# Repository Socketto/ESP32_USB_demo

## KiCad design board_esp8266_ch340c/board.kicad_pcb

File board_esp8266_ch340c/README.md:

# ESP8266 + CH340B USB board

Independent KiCad 10 project using an **ESP-12F** and a **CH340B** USB-to-UART
bridge. The ESP8266 + CP2102N project and its routed PCB are unchanged.

> **Prototype pending review.** The board is routed, but two USB connector
> hole-clearance errors and two via-in-pad locations remain. Obtain JLCPCB's
> acceptance of the USB geometry and review assembly risks before ordering.
> Electrical and thermal performance still require physical testing.

## Opening the project

Open `board.kicad_pro` in this directory. Keep `esp8266_usb.kicad_sym` and
`sym-lib-table` alongside it: they supply the local
`ESP8266_USB:CH340B_3V3` symbol.

The local symbol reflects the CH340B's pin functions. V3 pin 4 is a power
**input** in this externally supplied 3.3 V configuration, rather than the
regulator output used in 5 V operation.

## USB bridge and power

| Designator | Component | JLCPCB / LCSC |
| --- | --- | --- |
| U1 | Ai-Thinker ESP-12F | C82891 |
| U4 | WCH CH340B, SOP-16 | C81010 |
| U3 | TI TLV1117LV33DCYR, ceramic-stable 3.3 V regulator | C15578 |
| USB1 | HC-TYPE-C-16P-01A USB-C connector | C2894897 |
| D1 | ROHM SMLVN6RGB1U1 RGB LED, unchanged | C2909770 |

**C81010 is Extended**, not Basic. Check current stock, price and feeder
charges in the actual JLCPCB quotation. This variant does not substitute an
unverified Basic RGB 5050.

USB1 supplies +5V to U3. CH340B **VCC pin 16 and V3 pin 4 both connect to
+3V3**; neither connects to +5V. No crystal is required. Unlike CH340C,
CH340B pin 15 is the TNOW output and must not be connected to GND.

| CH340B pin | Connection |
| --- | --- |
| 1, GND | GND |
| 2, TXD | ESP8266 GPIO3 / U0RXD |
| 3, RXD | ESP8266 GPIO1 / U0TXD |
| 4, V3; 16, VCC | +3V3 |
| 5, UD+ | USB1 A6/B6 |
| 6, UD- | USB1 A7/B7 |
| 7, RST# | Unconnected; internal pull-up |
| 8-12 | Unused; intentionally left unconnected |
| 13, DTR# | PROG_DTR, transistor auto-reset circuit |
| 14, RTS# | PROG_RTS, transistor auto-reset circuit |
| 15, TNOW | Unconnected output |

The CP2102N-specific VBUS divider R14/R15 and reset pull-up R22 have been
removed, together with their schematic wiring and obsolete nets. CH340B
has internal power-on reset and needs neither circuit.

## Automatic programming

The existing two-MMBT3904 circuit is retained:

- DTR drives Q1's base through R18 (10 kOhm) and Q2's emitter.
- RTS drives Q2's base through R19 (10 kOhm) and Q1's emitter.
- Q1's collector controls ESP_EN; Q2's collector controls GPIO0.

| DTR pin level | RTS pin level | ESP_EN | GPIO0 |
| --- | --- | --- | --- |
| High | High | High | High |
| Low | Low | High | High |
| High | Low | Low | High |
| Low | High | High | Low |

These are **physical signal levels**, not serial API boolean values:
DTR#/RTS# are active low. The topology supports the ESP8266 `esptool`
automatic reset/download sequence without manual BOOT/RESET jumpers.
Disable terminal hardware flow control. Install the WCH CH340 driver if
the operating system does not provide it.

R5 (10 kOhm) and C6 (1 uF) set EN reset timing. R6 pulls GPIO0 high,
R13 pulls GPIO2 high, and R12 pulls GPIO15 low (all 10 kOhm).
Normal flash boot requires GPIO0/GPIO2 high and GPIO15 low; downloading
requires GPIO0 low at reset. ESP8266 EN and RST remain tied together as in
the source variant. Verify power-up, automatic uploads and the return to
normal boot on a physical prototype.

## Placement and routing

U4 now uses `Package_SO:SOIC-16_3.9x9.9mm_P1.27mm`, not the CP2102N QFN.
It is placed 1 mm below the former bridge position. C9 (100 nF) and C7
(4.7 uF) have been repositioned around it; C1 remains a 100 nF bypass.
Keep USB D+/D- together, short and away from the antenna. The revised D-
route follows D+ more closely, but the pair has not been impedance-controlled
or simulated.

C8 (100 nF) and C11 (4.7 uF) remain at ESP VCC. C6 remains near EN/RST.
Preserve the ESP-12F footprint's antenna keepout on both copper layers.
The +3V3 supply has a wider parallel B.Cu track and a local F.Cu copper
area at U3's tab. The long supply and remaining narrow segments still require
voltage-drop and temperature measurements under Wi-Fi load. Retain the
ceramic-stable TLV1117LV regulator and C5 (22 uF), rather than making an
unchecked AMS1117 substitution.

The board outline includes physical letter-shaped cutouts on Edge.Cuts;
check that these are intentional in JLCPCB's Gerber viewer. The ESP antenna
keepout and USB connector footprint, including its holes, are unchanged.

## Firmware connections

| Function | ESP8266 pin | Circuit |
| --- | --- | --- |
| RGB red | GPIO12 / D6 | R2, 330 Ohm, to red anode |
| RGB green | GPIO13 / D7 | R3, 330 Ohm, to green anode |
| RGB blue | GPIO14 / D5 | R1, 330 Ohm, to blue anode |
| Digital input | GPIO4 / D2 | IN1, active high; R8 external 10 kOhm pull-down |
| Analog input | TOUT / ADC0 / A0 | TH1 NTC and R23/R24/R25 divider |
| Recovery input | GPIO5 / D1 | DA1, normally open; close to GND during boot |

D1 retains its existing ROHM footprint and common-ground cathodes.
R1/R2/R3 remain 330 Ohm. Green and blue may be dim at 3.3 V; verify their
brightness on the prototype before changing resistors. A future 5050
substitution requires a verified part number, pinout, polarity and resistor
review.

TH1 is a 10 kOhm B3950 NTC. R23 (10 kOhm) supplies the thermistor divider;
R24 (33 kOhm) and R25 (10 kOhm) attenuate its output for the ESP8266's
0-1.0 V ADC. Including divider loading, nominal ADC voltage is about
0.344 V at 25 C and 0.623 V with an open thermistor. Firmware reads A0
as a raw 10-bit value, 0..1023, exposed as `REAL`; do not apply 3.3 V
directly to TOUT.

DA1 connects GPIO5 to GND for recovery, not to the ADC or ROM boot strap.
Firmware must enable GPIO5's pull-up and sample DA1 during boot to restore
the default application and parameters. DA1 remains excluded from the
assembly BOM and CPL.

## JLCPCB manufacturing files

Use **[bouni/kicad-jlcpcb-tools](https://github.com/bouni/kicad-jlcpcb-tools)**,
listed as *JLCPCB Tools* in KiCad's Plugin and Content Manager.
This variant has its own `jlcpcb/project.db` with U4 assigned to C81010
and R14/R15/R22 removed.

The database retains the transistor and ROHM LED orientation corrections.
It includes a `^CH340B$` rule of +270 degrees,
following the plugin's SOP/SOIC convention. With the current PCB angles,
U4 exports at 270 degrees, Q1/Q2 at 180 degrees and D1 at 180 degrees.
These are **CPL corrections**, not instructions to rotate the PCB footprints.
Confirm every component's pin 1 against JLCPCB's assembly preview.

The current exports are in `jlcpcb/production_files`: Gerber and drill ZIP,
BOM and CPL were generated from this PCB and its local plugin database.
Regenerate all of them together after any design change; do not mix them
with exports from the CP2102N or ESP32 projects. Inspect the Gerbers and
the placement preview, including pin 1 and polarity, before ordering.

## Images

Images are design previews, not fabrication approval.

## Current checks and remaining work

Schematic ERC: no errors; one inherited D4 LED-library mismatch warning.
PCB DRC: no unconnected items or schematic-parity issues; two USB1
hole-clearance errors remain. The clearance is 0.1847 mm versus the
project's 0.25 mm requirement. The connector holes have deliberately not
been changed: **JLCPCB must confirm that they can manufacture this geometry**.

Seventeen vias were moved outside SMD pads. Two remain in pads: U4 pin 5
(USB D+) and D4 pin 1 (GND). Although the vias are tented, the pad's mask
opening can expose the hole and cause solder wicking. Ask JLCPCB about
their assembly process or move/fill these vias before ordering.

Prototype checks must cover USB enumeration, both UART directions,
automatic programming/reset, ESP Wi-Fi power stability and regulator
temperature, RGB brightness, digital input, NTC ADC and firmware recovery.

References:
[WCH CH340 datasheet](https://www.wch-ic.com/downloads/CH340DS1_PDF.html) and
[Espressif ESP8266 boot mode selection](https://docs.espressif.com/projects/esptool/en/latest/esp8266/advanced-topics/boot-mode-selection.html);
[JLCPCB via-in-pad guidance](https://jlcpcb.com/blog/via-in-pad-pcb).

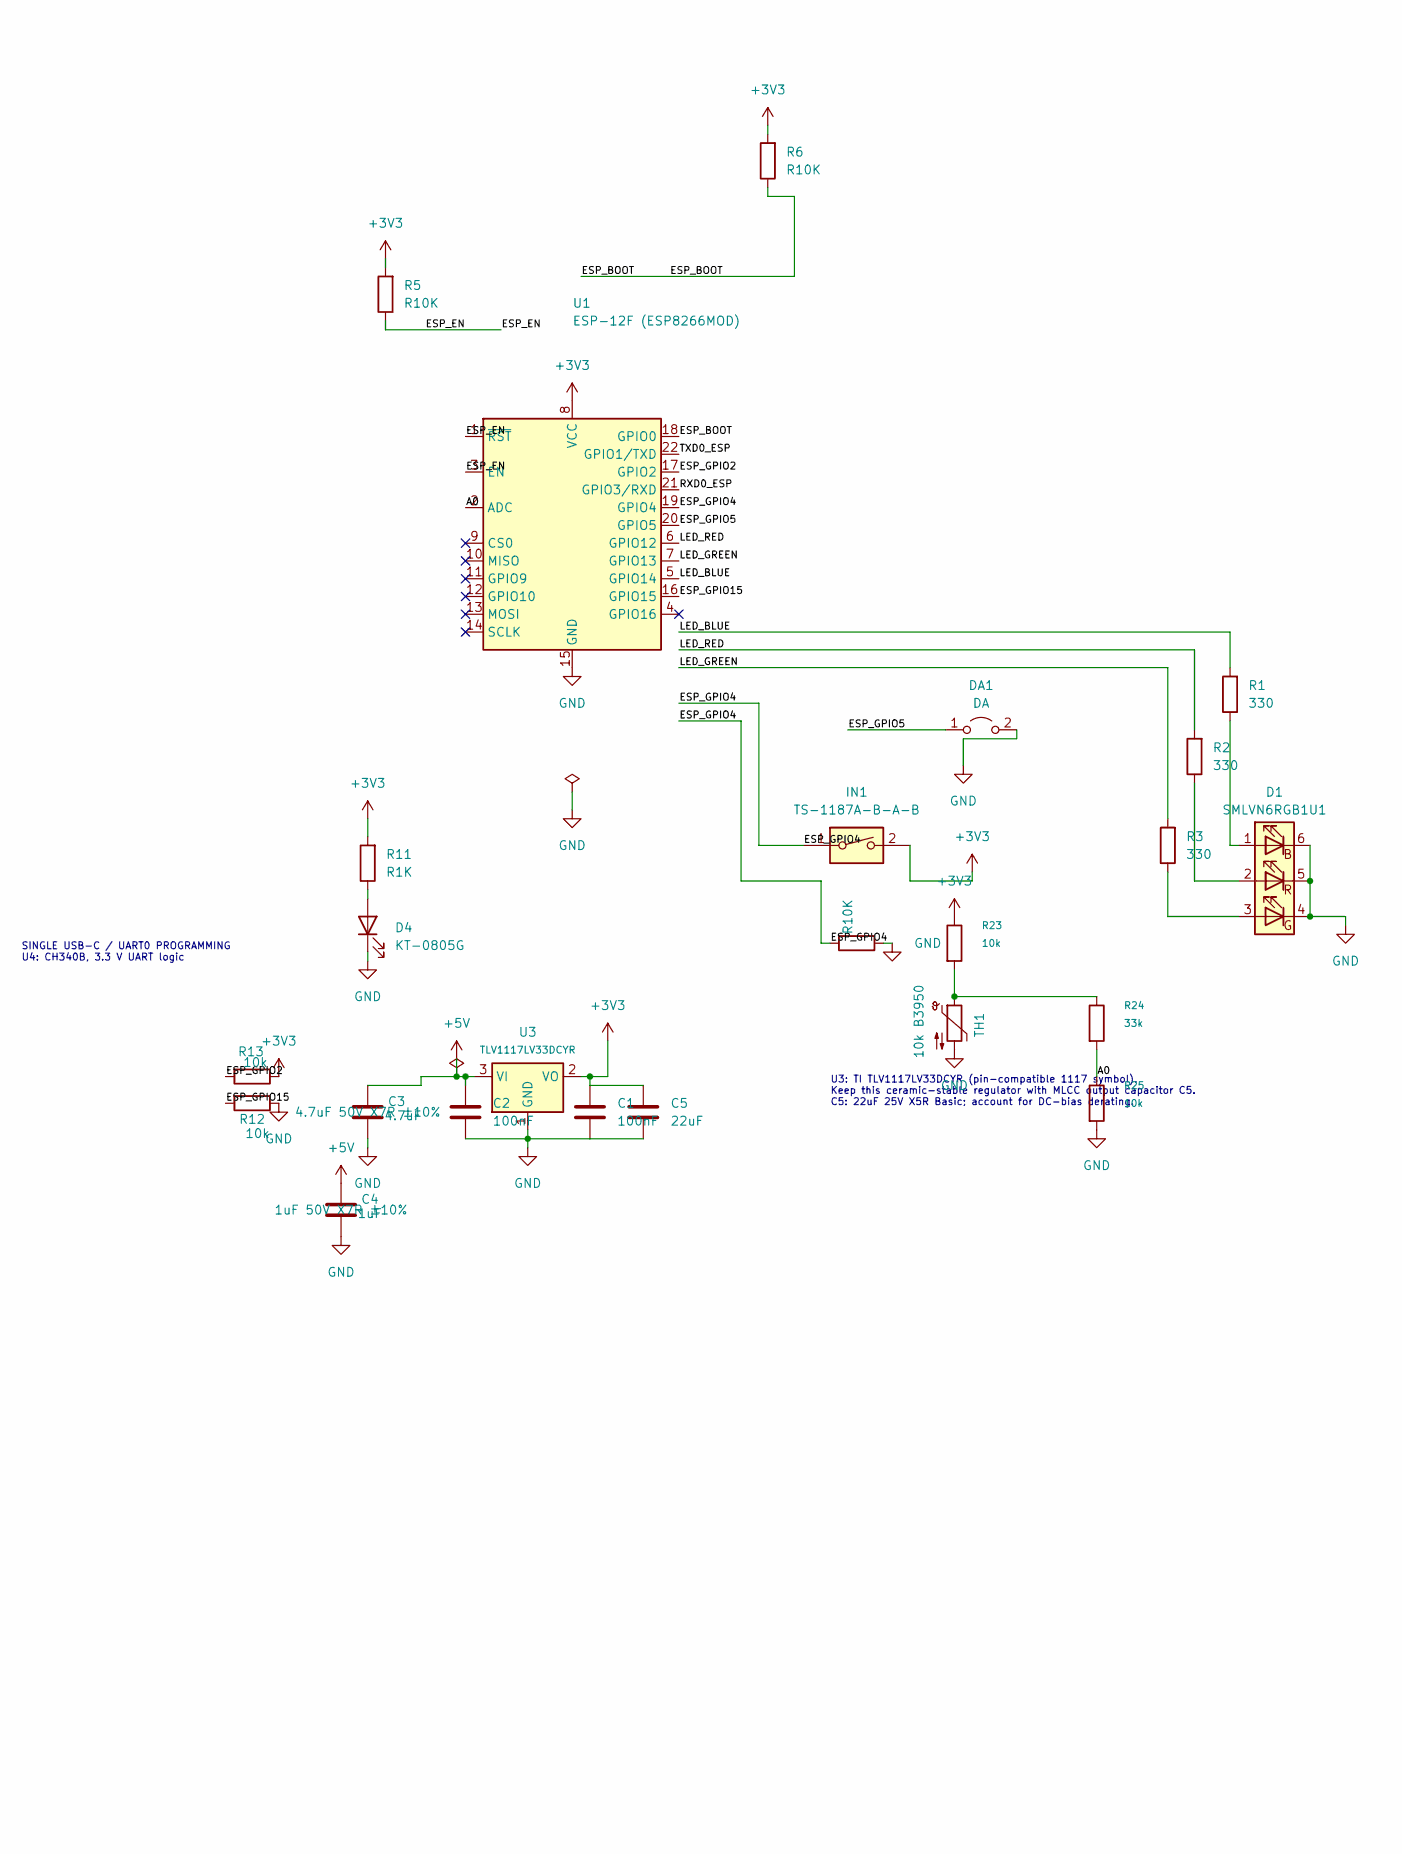
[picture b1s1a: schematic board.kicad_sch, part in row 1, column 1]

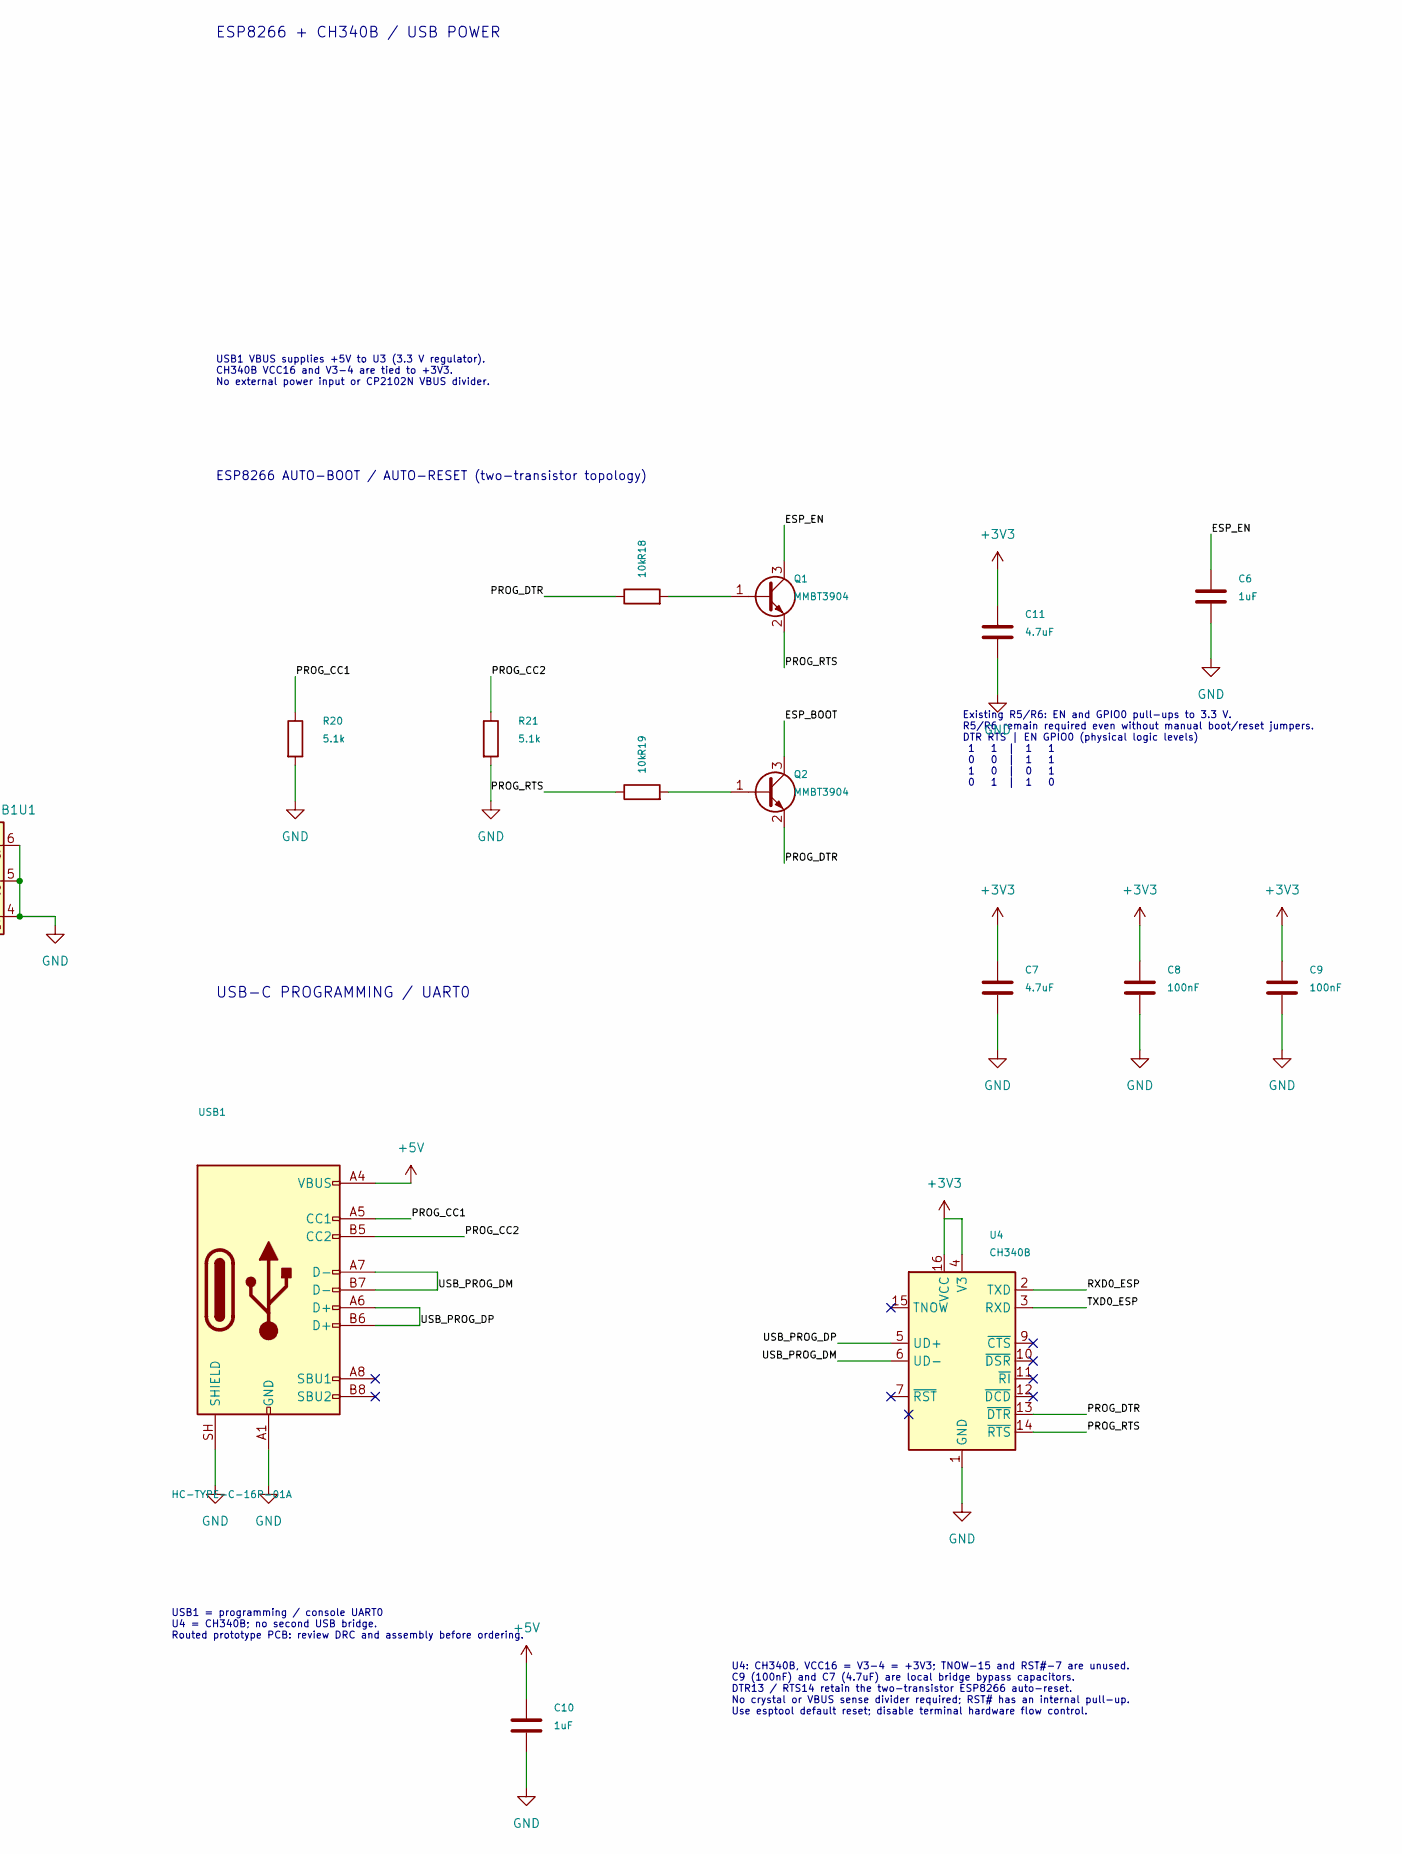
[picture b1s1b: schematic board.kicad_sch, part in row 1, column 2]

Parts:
C1, C2, C8, C9: 100nF; C_1206_3216Metric; MPN CL31B104KBCNNNC; LCSC C24497
C3, C7, C11: 4.7uF; C_1206_3216Metric; MPN 1206B475K500NT; LCSC C29823
C4, C6, C10: 1uF; C_1206_3216Metric; MPN CL31B105KBHNNNE; LCSC C1848
C5: 22uF; C_1206_3216Metric; MPN CL31A226KAHNNNE; LCSC C12891
D1: SMLVN6RGB1U1; LED_ROHM_SMLVN6; MPN SMLVN6RGB1U1; LCSC C2909770
D4: KT-0805G; LED_0805_2012Metric; MPN KT-0805G; LCSC C2297
DA1: DA; PinHeader_2x01_P2.54mm_Vertical
IN1: TS-1187A-B-A-B; SW_Push_1P1T_XKB_TS-1187A; MPN TS-1187A-B-A-B; LCSC C318884
Q1, Q2: MMBT3904; SOT-23; MPN MMBT3904(RANGE:100-300); LCSC C20526
R1, R2, R3: 330; R_1206_3216Metric; MPN 1206W4F3300T5E; LCSC C17930
R5, R6, R8: R10K; R_1206_3216Metric; MPN 1206W4F1002T5E; LCSC C17902
R11: R1K; R_1206_3216Metric; MPN 1206W4F1001T5E; LCSC C4410
R12, R13, R25: 10k; R_0603_1608Metric; MPN 0603WAF1002T5E; LCSC C25804
R18, R19, R23: 10k; R_1206_3216Metric; MPN 1206W4F1002T5E; LCSC C17902
R20, R21: 5.1k; R_0603_1608Metric; MPN 0603WAF5101T5E; LCSC C23186
R24: 33k; R_0603_1608Metric; MPN 0603WAF3302T5E; LCSC C4216
TH1: 10k B3950; R_0805_2012Metric; MPN CMFB103J3950HANT; LCSC C338623
U1: ESP-12F (ESP8266MOD); ESP-12E; MPN ESP-12F(ESP8266MOD); LCSC C82891
U3: TLV1117LV33DCYR; SOT-223-3_TabPin2; MPN TLV1117LV33DCYR; LCSC C15578
U4: CH340B; SOIC-16_3.9x9.9mm_P1.27mm; MPN CH340B; LCSC C81010
USB1: HC-TYPE-C-16P-01A; USB_C_Receptacle_HCTL_HC-TYPE-C-16P-01A; MPN HC-TYPE-C-16P-01A; LCSC C2894897

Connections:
+3V3: C1.1, C5.1, C7.1, C8.1, C9.1, C11.1, IN1.2, R5.2, R6.2, R11.2, R13.1, R23.1, U1.8 (VCC), U3.2 (VO), U4.4 (V3), U4.16 (VCC)
+5V: C2.1, C3.1, C4.1, C10.1, U3.3 (VI), USB1.A4 (VBUS), USB1.A9 (VBUS), USB1.B4 (VBUS), USB1.B9 (VBUS)
/A0: R24.2, R25.1, U1.2 (ADC)
/ESP_BOOT: Q2.3 (C), R6.1, U1.18 (GPIO0)
/ESP_EN: C6.1, Q1.3 (C), R5.1, U1.1 (~RST), U1.3 (EN)
/ESP_GPIO2: R13.2, U1.17 (GPIO2)
/ESP_GPIO4: IN1.1, R8.2, U1.19 (GPIO4)
/ESP_GPIO5: DA1.1 (A), U1.20 (GPIO5)
/ESP_GPIO15: R12.2, U1.16 (GPIO15)
/LED_BLUE: R1.2, U1.5 (GPIO14)
/LED_GREEN: R3.2, U1.7 (GPIO13)
/LED_RED: R2.2, U1.6 (GPIO12)
/PROG_CC1: R20.1, USB1.A5 (CC1)
/PROG_CC2: R21.1, USB1.B5 (CC2)
/PROG_DTR: Q2.2 (E), R18.1, U4.13 (~DTR)
/PROG_RTS: Q1.2 (E), R19.1, U4.14 (~RTS)
/RXD0_ESP: U1.21 (GPIO3/RXD), U4.2 (TXD)
/TXD0_ESP: U1.22 (GPIO1/TXD), U4.3 (RXD)
/USB_PROG_DM: U4.6 (UD-), USB1.A7 (D-), USB1.B7 (D-)
/USB_PROG_DP: U4.5 (UD+), USB1.A6 (D+), USB1.B6 (D+)
GND: C1.2, C2.2, C3.2, C4.2, C5.2, C6.2, C7.2, C8.2, C9.2, C10.2, C11.2, D1.4 (GK), D1.5 (RK), D1.6 (BK), D4.1 (K), DA1.2 (B), R8.1, R12.1, R20.2, R21.2, R25.2, TH1.2, U1.15 (GND), U3.1 (GND), U4.1 (GND), USB1.A1 (GND), USB1.A12 (GND), USB1.B1 (GND), USB1.B12 (GND), USB1.SH (SHIELD)
unnamed: D1.1 (BA), R1.1
unnamed: D1.3 (GA), R3.1
unnamed: D1.2 (RA), R2.1
unnamed: D4.2 (A), R11.1
unnamed: Q1.1 (B), R18.2
unnamed: Q2.1 (B), R19.2
unnamed: R23.2, R24.1, TH1.1

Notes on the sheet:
SINGLE USB-C / UART0 PROGRAMMING U4: CH340B, 3.3 V UART logic
ESP8266 + CH340B / USB POWER
USB1 = programming / console UART0 U4 = CH340B; no second USB bridge. Routed prototype PCB: review DRC and assembly before ordering.
USB-C PROGRAMMING / UART0
USB1 VBUS supplies +5V to U3 (3.3 V regulator). CH340B VCC16 and V3-4 are tied to +3V3. No external power input or CP2102N VBUS divider.
U4: CH340B, VCC16 = V3-4 = +3V3; TNOW-15 and RST#-7 are unused. C9 (100nF) and C7 (4.7uF) are local bridge bypass capacitors. DTR13 / RTS14 retain the two-transistor ESP8266 auto-reset. No crystal or VBUS sense divider required; RST# has an internal pull-up. Use esptool default reset; disable termi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
U3: TI TLV1117LV33DCYR (pin-compatible 1117 symbol). Keep this ceramic-stable regulator with MLCC output capacitor C5. C5: 22uF 25V X5R Basic; account for DC-bias derating.
ESP8266 AUTO-BOOT / AUTO-RESET (two-transistor topology)
Existing R5/R6: EN and GPIO0 pull-ups to 3.3 V. R5/R6 remain required even without manual boot/reset jumpers. DTR RTS | EN GPIO0 (physical logic levels) 1 1 | 1 1 0 0 | 1 1 1 0 | 0 1 0 1 | 1 0

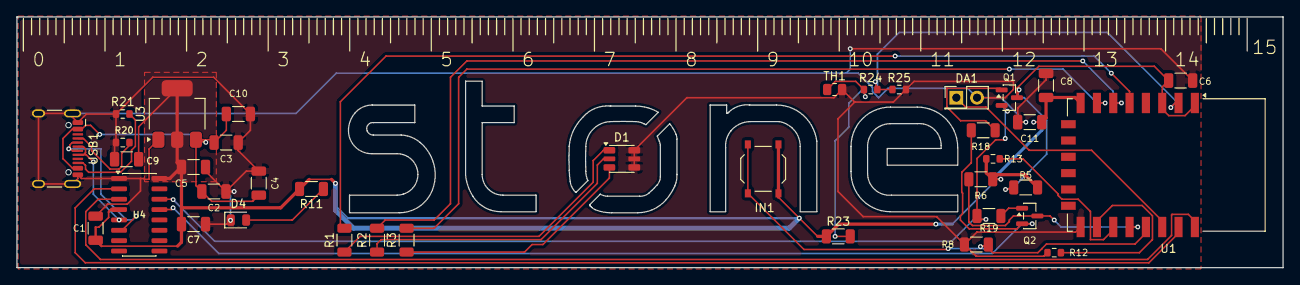
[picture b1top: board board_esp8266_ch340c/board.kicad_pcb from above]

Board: 2 copper layers, 155.2 x 30.7 mm, 38 parts (0 on the bottom side), 28 nets.

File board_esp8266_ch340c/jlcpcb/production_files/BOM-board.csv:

Comment,Designator,Footprint,LCSC,Quantity
100nF,"C1,C2,C8,C9",C_1206_3216Metric,C24497,4
10k,"R18,R19,R23",R_1206_3216Metric,C17902,3
10k,"R12,R13,R25",R_0603_1608Metric,C25804,3
10k B3950,TH1,R_0805_2012Metric,C338623,1
1uF,"C10,C4,C6",C_1206_3216Metric,C1848,3
22uF,C5,C_1206_3216Metric,C12891,1
330,"R1,R2,R3",R_1206_3216Metric,C17930,3
33k,R24,R_0603_1608Metric,C4216,1
4.7uF,"C11,C3,C7",C_1206_3216Metric,C29823,3
5.1k,"R20,R21",R_0603_1608Metric,C23186,2
CH340B,U4,SOIC-16_3.9x9.9mm_P1.27mm,C81010,1
ESP-12F (ESP8266MOD),U1,ESP-12E,C82891,1
HC-TYPE-C-16P-01A,USB1,USB_C_Receptacle_HCTL_HC-TYPE-C-16P-01A,C2894897,1
KT-0805G,D4,LED_0805_2012Metric,C2297,1
MMBT3904,"Q1,Q2",SOT-23,C20526,2
R10K,"R5,R6,R8",R_1206_3216Metric,C17902,3
R1K,R11,R_1206_3216Metric,C4410,1
SMLVN6RGB1U1,D1,LED_ROHM_SMLVN6,C2909770,1
TLV1117LV33DCYR,U3,SOT-223-3_TabPin2,C15578,1
TS-1187A-B-A-B,IN1,SW_Push_1P1T_XKB_TS-1187A,C318884,1

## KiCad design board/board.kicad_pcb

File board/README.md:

# ESP32 USB demo - KiCad board

ESP32-WROOM-32E-N4 demonstration board with one USB-C port, a WCH CH340C
application USB-to-UART bridge, external UART0 programming headers, a 3.3 V
regulator, and a TFT SPI connector.

> **Work in progress, not production-ready.** The PCB has no tracks, vias,
> or copper zones. Exported Gerber, BOM, and CPL files are placement snapshots,
> not a finished board suitable for ordering. Complete routing and resolve
> manufacturing issues before fabrication.
>
> **Connect either the external programmer or Serial1 USB, never both.**
> During programming, the programmer supplies regulated 3.3 V through J2.
> Disconnect the programmer completely before connecting Serial1 USB.
> UART signals must use 3.3 V logic, never 5 V or RS-232 voltages.

## Overview

*Component placement, not a routed board.*

| Block | Components and function |
| --- | --- |
| Microcontroller | U1, ESP32-WROOM-32E-N4, Wi-Fi/Bluetooth and 4 MB flash |
| Application USB-C | Serial1 and U2 CH340C, connected to ESP32 UART2; R12/R13 are the USB-C CC pull-downs |
| External programming | J2 exposes UART0, EN/reset, GPIO0/BOOT, ground and the common +3V3 rail |
| Manual boot/reset | Use J2 pin 6 (GPIO0), pin 5 (EN) and pin 2 (GND); no separate BOOT/RESET headers |
| Boot/reset bias | R5/R6, 10 kOhm EN/GPIO0 pull-ups; C6, 1 uF EN-to-ground reset timing |
| Power | U3 USB regulator output and J2 pin 1 share +3V3 directly; no source selector or reverse-current isolation |
| Display | J1, 8-pin TFT SPI header |
| Indicators and inputs | D1 RGB LED, IN1 push button, TH1 10 kOhm B3950 NTC |
| Configuration | DA1 solder jumper |

The second programming USB connector FLASHER1, its CH340C U4, automatic-reset
transistors Q1/Q2, and associated R18/R19/R20/R21/C7/C8/C10 have been removed.
Serial1 remains the **application UART2 interface**, not the ESP32 ROM
programming interface. UART2 requires matching firmware configuration.
There is no on-board DTR/RTS auto-reset circuit in this revision.

The independent [`board_cp2102n` project](../board_cp2102n/README.md) has not
been changed: it retains two CP2102N bridges, two USB-C connectors, and
automatic programming. The two projects therefore no longer differ only
in bridge choice; account for these functional differences when comparing
JLCPCB quotations.

## External programming

J2 uses a six-pin, through-hole, 2.54 mm vertical header. The table gives
**KiCad pad numbers**, not an assumed left-to-right connector view; pad 1
is square. Board labels TX/RX refer to the ESP32, not the adapter.

| J2 pin | Signal | External adapter connection |
| --- | --- | --- |
| 1 | +3V3, common board rail | Programmer's regulated 3.3 V output; Serial1 USB must be disconnected |
| 2 | GND | Adapter GND |
| 3 | TXD0_ESP, GPIO1/U0TXD | Adapter RX input |
| 4 | RXD0_ESP, GPIO3/U0RXD | Adapter TX output |
| 5 | ESP_EN, reset | Briefly connect to pin 2 (GND), then release to reset |
| 6 | ESP_BOOT, GPIO0 | Connect to pin 2 (GND) during reset to enter download mode |

J2 pin 1, U3's output and the board loads are directly connected to the same
`+3V3` rail. No power-selection jumper is required. This arrangement assumes
physically exclusive connections: unplug Serial1 USB for programming, then
disconnect the programmer completely before using Serial1 USB.

BOOT and RESET are operated directly through J2; separate BOOT1/RST1 headers
are not fitted. Use temporary leads to GND as described below; do not keep EN
grounded during flashing or normal operation.
R5/R6 remain necessary even without auto-reset: they establish the normal
high levels of EN and GPIO0. C6 remains connected between EN and GND.

### Manual flashing sequence

1. Make sure Serial1 USB is disconnected and all power is off.
2. Connect a regulated **3.3 V supply** to J2 pin 1 and GND to pin 2.
   The supply must support the ESP32's current peaks and other board loads;
   many USB-to-UART adapter 3.3 V outputs are not rated for this load.
   Connect a 3.3 V logic USB-to-UART adapter's GND, RX and TX as shown above.
   Use a common ground. Do not connect Serial1 USB while the programmer is connected.
3. Connect J2 pin 6 to pin 2 (GND) to pull GPIO0 low.
4. Briefly connect J2 pin 5 to GND, then release it while keeping GPIO0 low. The ESP32
   enters its ROM serial download mode when EN rises.
5. Select the **external adapter's** serial port in `esptool` or the IDE,
   not Serial1/U2. Use manual boot/reset handling rather than expecting an
   on-board DTR/RTS reset circuit. Disable RTS/CTS hardware flow control.
6. After flashing, release GPIO0 and disconnect the programmer and any external
   supply completely. Connect Serial1 USB to run the application.

For normal USB operation, leave J2 GPIO0 and EN released.
EN and GPIO0 are exposed
for a suitable external programming circuit, but **do not directly wire
adapter DTR/RTS to them** without a correctly designed ESP32 reset circuit.
The adapter's driver depends on its bridge; the on-board U2 uses the WCH
CH340/CH341 driver.

### TFT SPI pinout

| J1 pin | Signal |
| --- | --- |
| 1 | +3V3 |
| 2 | GND |
| 3 | SPI_CS |
| 4 | SPI_RESET |
| 5 | SPI_DC |
| 6 | SPI_SDA, SPI data |
| 7 | SPI_SCK |
| 8 | +3V3 |

Check that the display accepts 3.3 V power and logic. `SPI_SDA` is the
SPI data net name here, not an I2C connection.

## CH340C, USB and power

U2 uses CH340C, **C84681**, in
`Package_SO:SOIC-16_3.9x9.9mm_P1.27mm`. It is not pin-compatible with
CP2102N. Its application UART operates at ESP32-safe 3.3 V logic levels.

| U2 pin | Connection |
| --- | --- |
| 16, VCC and 4, V3 | Both tied to regulated +3V3 |
| 1, GND and 15, R232 | Ground; normal non-inverted TTL UART mode |
| 5, UD+ and 6, UD- | Serial1 D+ and D-, respectively |
| 2, TXD and 3, RXD | Application UART2, with TX/RX crossed to the ESP32 |
| 7-14 | Unused clock/OUT/modem/control pins |

This is the manufacturer's **external 3.3 V supply mode**. Do not apply
5 V to VCC while V3 remains tied to it. C9 supplies local 100 nF bypass
decoupling; route its ground return and the bridge supply connections short.
CH340C has an internal clock and power-on reset, and no VBUS-sense input.
The former CP2102N reset pull-ups R7/R22 and sensing divider R14/R15
are absent. See the [WCH CH340 datasheet](https://www.lcdwiki.com/res/PublicFile/CH340C_en.pdf).

Serial1 D+ (A6/B6) and D- (A7/B7) connect directly to U2 pins 5 and 6.
No external series USB resistors or USB pull-up are required. There is no
external USB data-line ESD array, reducing protection against connector
electrostatic discharge. Route the differential pair appropriately.
With only one board USB connector, the former dual-VBUS power-sharing
restriction no longer applies to this project. Respect USB host current
limits and the ESP32/display power budget.

U3 remains **TI TLV1117LV33DCYR**, with the pin-compatible 1117 symbol and
SOT-223 footprint. Its maximum operating input is 5.5 V. Keep this
ceramic-stable TI regulator rather than substituting a generic AMS1117
without checking stability. C5 is nonpolar 22 uF / 25 V X5R ceramic 1206;
allow for DC-bias/temperature derating and retain at least the regulator's
required effective capacitance. During external programming, U3's OUT remains
connected to +3V3 while its USB input is floating. Its internal body diode
can charge the input capacitors and raise the disconnected VBUS rail below
the external 3.3 V supply. There is no reverse-current isolation; verify the
startup transient on assembled hardware, especially if adding VBUS loads.
TI documents that reverse current is not internally limited; see the
[TLV1117LV datasheet, section 7.3.1](https://www.ti.com/lit/ds/symlink/tlv1117lv.pdf).

## Schematic and files

*Open the image to zoom in. KiCad sources are authoritative.*

| Path | Contents |
| --- | --- |
| `board.kicad_pro` | KiCad project to open |
| `board.kicad_sch` | Schematic |
| `board.kicad_pcb` | Unrouted PCB placement |
| `esp32_usb.kicad_sym`, `sym-lib-table` | Project CH340C symbol for external 3.3 V supply mode |
| `images/` | README schematic and PCB snapshots |
| `jlcpcb/project.db` | Plugin assignments, export exclusions and local corrections |
| `jlcpcb/gerber/` | Generated Gerber and drill files |
| `jlcpcb/production_files/` | Generated Gerber archive, BOM and CPL |

Sources use **KiCad 10**. Install standard symbol and footprint libraries;
the schematic also embeds a connector symbol originating from
`PCM_JLCPCB-Extended`. Serial1 uses
`Connector_USB:USB_C_Receptacle_HCTL_HC-TYPE-C-16P-01A`.
The local `ESP32_USB:CH340C_3V3` symbol represents V3 as a power input,
matching external 3.3 V operation and avoiding a false ERC power-output
conflict. Keep both local-library files with the project.

Generated `jlcpcb/gerber/` and `jlcpcb/production_files/` directories are
ignored by Git. Regenerate from current sources before uploading. Keep
the plugin database and documentation images under version control.
Editor history, lock files, autosaves and `*.kicad_prl` are also ignored.

## Required KiCad plugin for JLCPCB

Use **[bouni/kicad-jlcpcb-tools](https://github.com/bouni/kicad-jlcpcb-tools)**,
shown in KiCad as **JLCPCB Tools**. It assigns LCSC/JLCPCB parts and generates
Gerber, Excellon, BOM and CPL files. *Fabrication Toolkit* is a different
plugin and may apply different rotation corrections.

### Installation

1. Open KiCad's **Plugin and Content Manager**, then its repository manager.
2. Add the author's repository:

   ```text
   https://raw.githubusercontent.com/Bouni/bouni-kicad-repository/main/repository.json
   ```

3. Install **KiCad JLCPCB tools**, then restart the PCB Editor or refresh plugins.
4. Open **Tools > External Plugins > JLCPCB Tools**.

See the [official installation documentation](https://github.com/bouni/kicad-jlcpcb-tools#installation-)
for current requirements and interface changes.

### Main catalog assignments

| Reference | Manufacturer part | JLCPCB | Notes |
| --- | --- | --- | --- |
| U1 | ESP32-WROOM-32E-N4 | [C701341](https://jlcpcb.com/partdetail/C701341) | ESP32 module |
| U2 | CH340C | [C84681](https://jlcpcb.com/partdetail/C84681) | WCH SOP-16, internal clock |
| U3 | TLV1117LV33DCYR | [C15578](https://jlcpcb.com/partdetail/C15578) | Ceramic-stable TI regulator |
| C3 | 1206B475K500NT | [C29823](https://jlcpcb.com/partdetail/C29823) | Basic, 4.7 uF / 50 V X7R, 1206 |
| C4, C6 | CL31B105KBHNNNE | [C1848](https://jlcpcb.com/partdetail/C1848) | Basic, 1 uF / 50 V X7R, 1206 |
| C5 | CL31A226KAHNNNE | [C12891](https://jlcpcb.com/partdetail/C12891) | Basic, nonpolar 22 uF / 25 V X5R, 1206 |
| R12, R13 | 0603WAF5101T5E | [C23186](https://jlcpcb.com/partdetail/C23186) | Basic, 5.1 kOhm 1%, USB CC pull-downs |
| Serial1 | HC-TYPE-C-16P-01A | [C2894897](https://jlcpcb.com/partdetail/C2894897) | HCTL USB-C, matching footprint |
| J1, J2 | Standard 2.54 mm pin headers | Unassigned | Source and assemble manually |

J2 remains in the schematic and PCB but is **excluded from both BOM and CPL**
because it is manually assembled and has no assigned LCSC part. This prevents
JLCPCB reporting a BOM designator missing from the CPL. Source manual headers
separately, or deliberately select compatible catalog parts and a supported
through-hole assembly service before changing exclusions.

Existing cost-reduced Basic passive assignments are retained. The previous
dual-CH340C component estimate of USD 32.75 for five boards is **historical,
not the current BOM total**. This revision removes eleven components per
board and adds three manually assembled headers. Five remaining CH340C
devices use a different catalog quantity tier than ten devices: in the
previous snapshot, USD 0.546 instead of USD 0.456 each.
Removing one of two identical bridges does not remove its feeder code.
Compare freshly uploaded BOMs for actual component, assembly, feeder and
possible QFN X-ray charges; header/shunt sourcing, shipping and taxes are
additional. See [JLCPCB assembly pricing](https://jlcpcb.com/help/article/pcb-assembly-price).

### Export and upload

1. Save sources, update PCB from schematic as needed, and finish routing.
2. Run ERC and DRC, including schematic parity, and resolve errors.
3. Open JLCPCB Tools; check assignments, footprints, BOM/CPL exclusions and
   local corrections. Schematic fields alone may not update stored assignments.
4. Generate all outputs from the same PCB revision and plugin.
5. Upload `GERBER-board.zip`, `BOM-board.csv` and `CPL-board.csv` from
   `jlcpcb/production_files/`.
6. Inspect centering, assembly side, IC pin 1, lead alignment and LED polarity
   in JLCPCB's preview. Verify that removed programming components are absent.

Do not mix versions or upload old `production` exports. Negative CPL Y
coordinates are not inherently incorrect; they must match the Gerber origin.

### D1 RGB LED placement correction

The [ROHM SMLVN6RGB1U1 datasheet, Figure 1](https://fscdn.rohm.com/en/products/databook/datasheet/opto/led/chip_multi/smlvn6rgb1u1-e.pdf)
places the anode index at the upper-left corner in top view: pins 1/2/3 are
the blue/red/green anodes on the left, and pins 6/5/4 are their cathodes on
the right. The KiCad footprint and schematic use this mapping correctly.

The supplied JLCPCB preview with the original 0-degree CPL placed the
orientation marker at the opposite, lower-right corner. The local exact-value
rule `^SMLVN6RGB1U1$` therefore applies **180 degrees with zero X/Y offsets**.
D1 remains at 0 degrees in KiCad and exports at 180 degrees in the CPL.
This is an assembly-export correction, not a change to the physical footprint
or electrical connections. Re-upload the regenerated CPL and confirm the
model's anode index aligns with the upper-left pin-1 mark before ordering.
The corrected JLCPCB preview has not yet been confirmed.

### U2 placement correction

U2 retains the existing `^SOIC-` **270-degree package correction**. At its
0-degree PCB orientation, the CPL exports 270 degrees. This changes export
orientation, not the footprint's physical placement. Confirm CH340C pin 1
and lead alignment in the JLCPCB preview; the old CP2102N preview cannot
validate the current SOP-16 device.

The historical exact-value CP2102N and MMBT3904 rules remain in
`project.db`, but no current component matches them. Q1/Q2 are removed.
Keep the database: in this plugin version, local rules **replace**, rather
than extend, the global correction table. Global rules were copied locally
to preserve other packages' behavior. Recheck after updates or part changes.

## Open issues before fabrication

- **Routing is missing:** no tracks, vias or zones; unconnected pads remain.
- **Serial1:** existing HCTL hole-to-copper clearances are approximately
  0.185 mm against the project's 0.25 mm minimum. Correct geometry or confirm
  manufacturing requirements; do not lower constraints just to hide errors.
- **U1:** footprint 0.2 mm holes are below the project's 0.3 mm drill minimum;
  verify footprint/process requirements.
- **Silkscreen and assembly:** existing overlaps remain; confirm U2
  orientation in the assembly preview.
- **Schematic libraries:** existing embedded-symbol/library warnings and
  unused ESP32 GPIO findings remain to be resolved or explicitly reviewed.

The images and local outputs reflect the external-programming revision.
Regenerate them after further source changes.

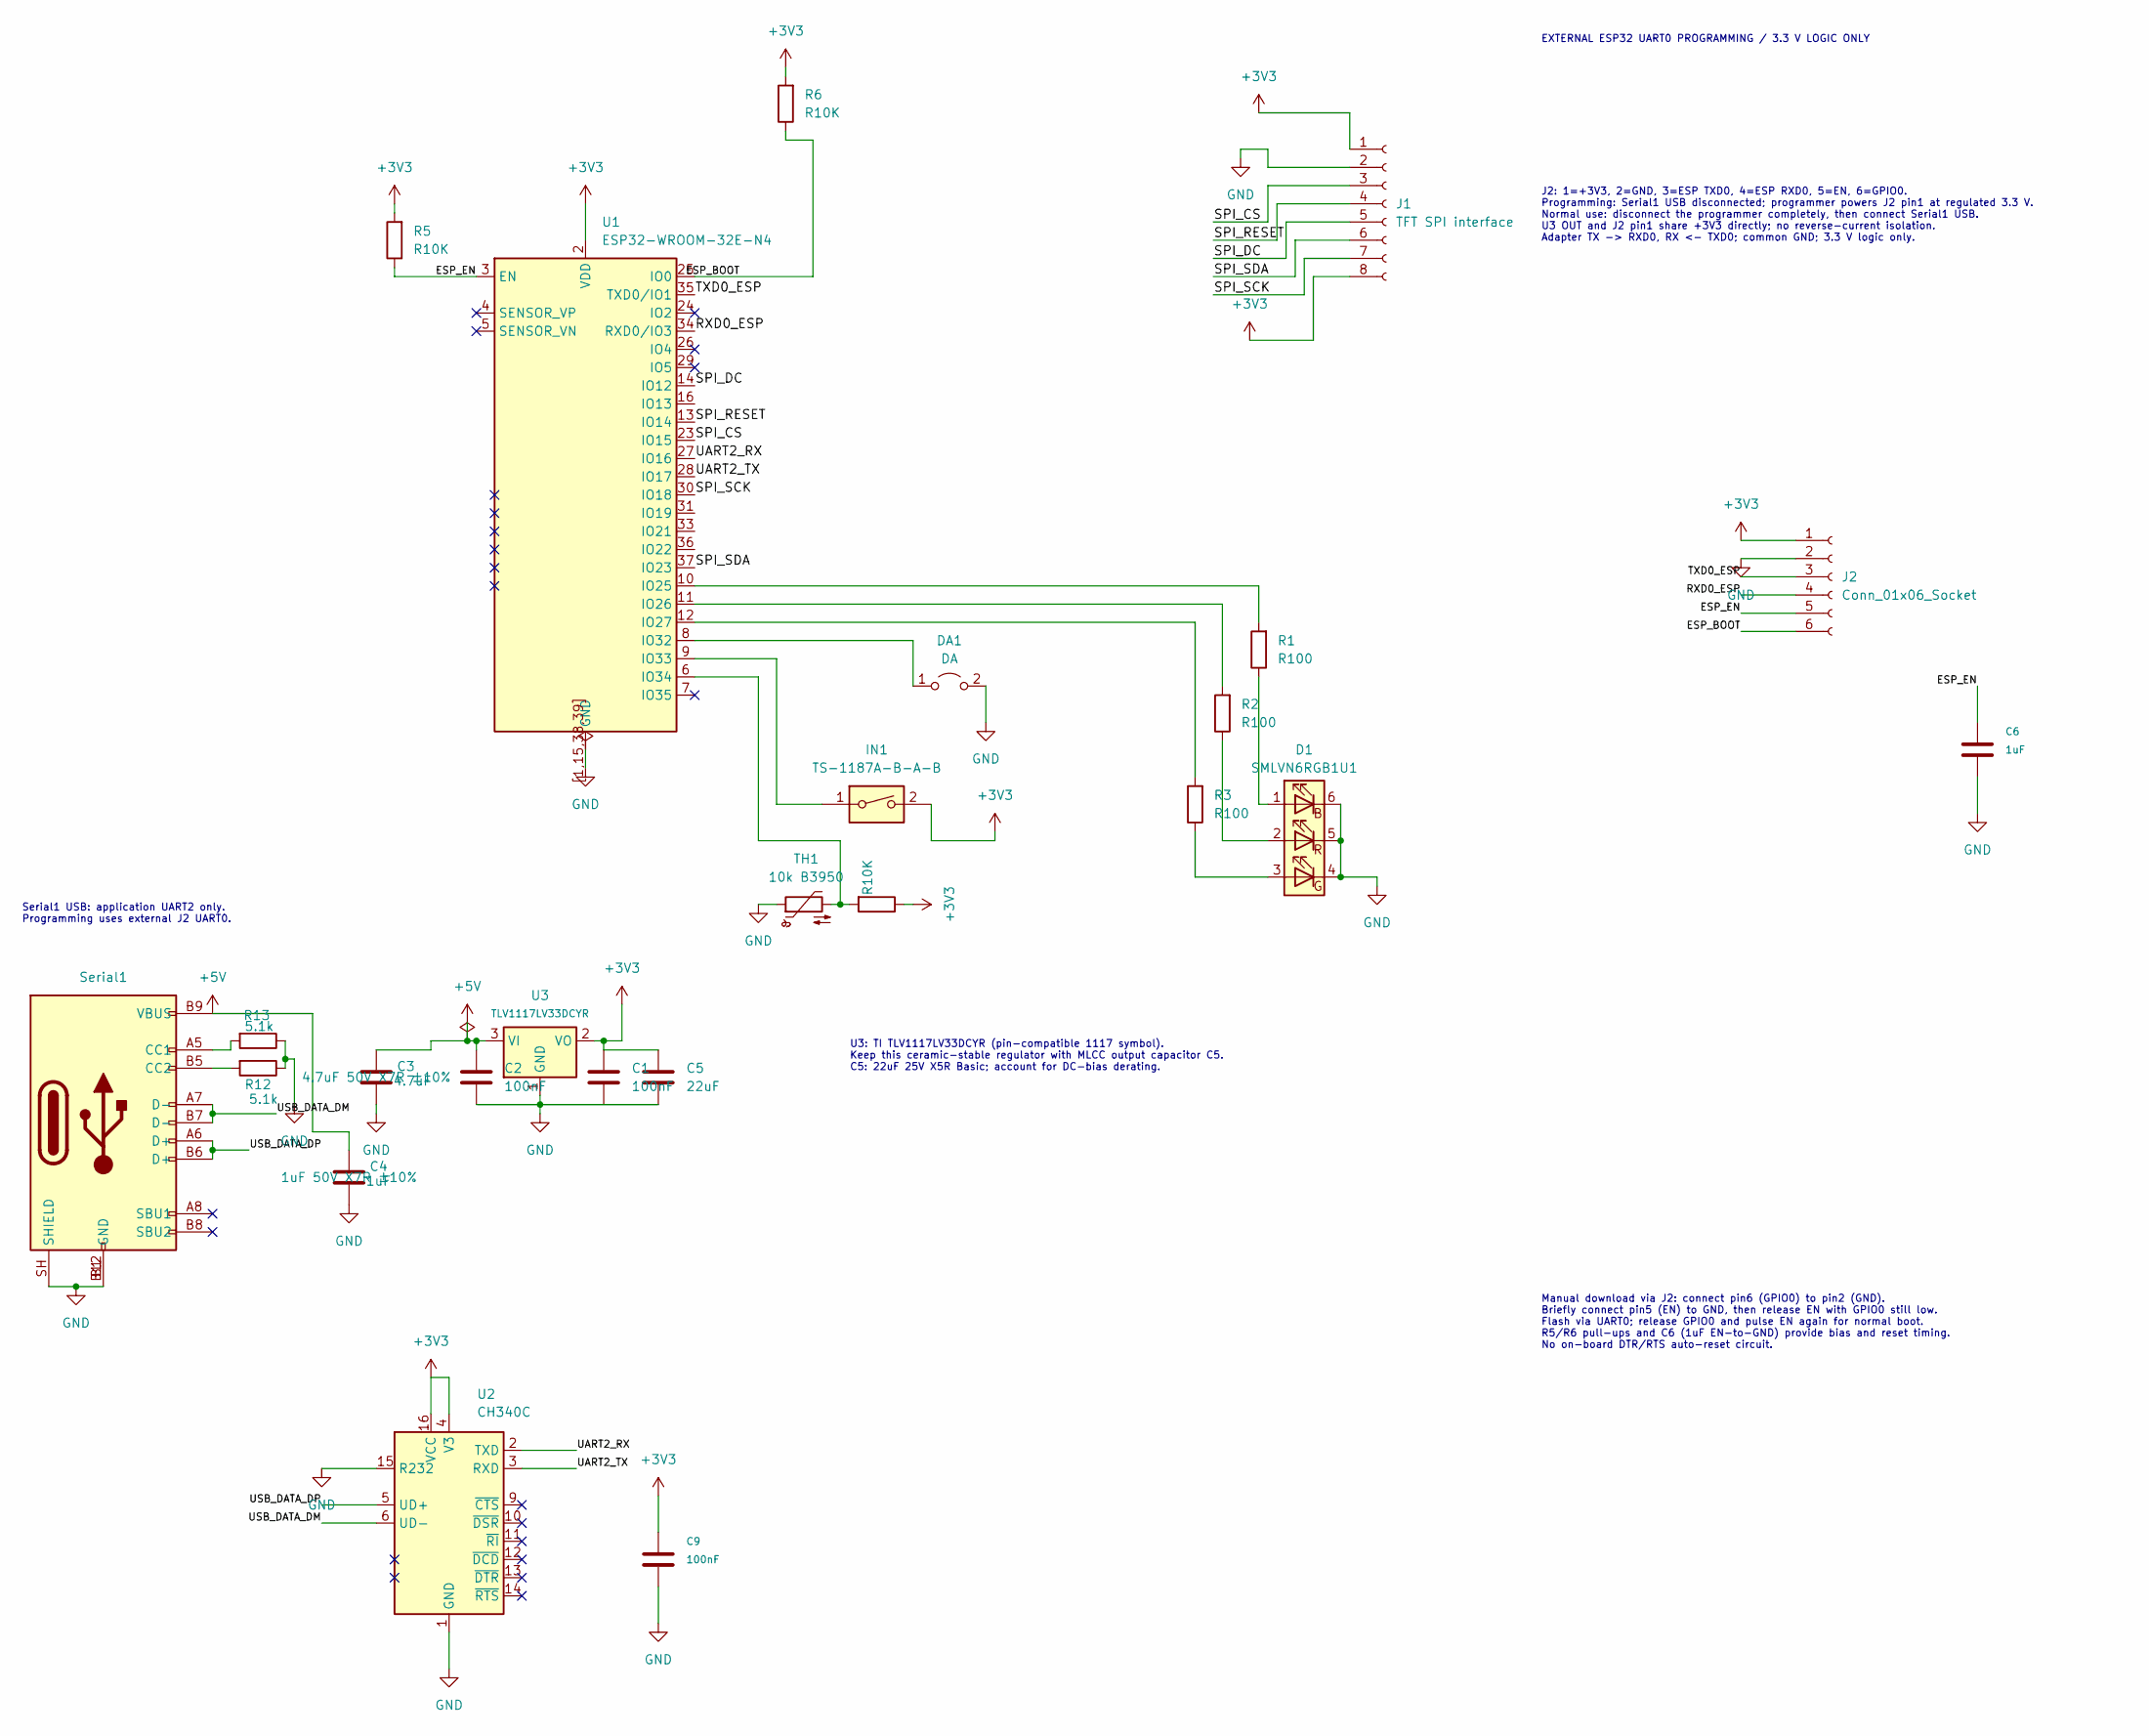
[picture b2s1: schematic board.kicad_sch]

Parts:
C1, C2, C9: 100nF; C_1206_3216Metric; MPN CL31B104KBCNNNC; LCSC C24497
C3: 4.7uF; C_1206_3216Metric; MPN 1206B475K500NT; LCSC C29823
C4, C6: 1uF; C_1206_3216Metric; MPN CL31B105KBHNNNE; LCSC C1848
C5: 22uF; C_1206_3216Metric; MPN CL31A226KAHNNNE; LCSC C12891
D1: SMLVN6RGB1U1; LED_ROHM_SMLVN6; MPN SMLVN6RGB1U1; LCSC C2909770
DA1: DA; PinHeader_1x02_P2.54mm_Vertical
IN1: TS-1187A-B-A-B; SW_Push_1P1T_XKB_TS-1187A; MPN TS-1187A-B-A-B; LCSC C318884
J1: TFT SPI interface; PinHeader_1x08_P2.54mm_Vertical
J2: Conn_01x06_Socket; PinHeader_1x06_P2.54mm_Vertical
R1, R2, R3: R100; R_1206_3216Metric; MPN 1206W4F1000T5E; LCSC C17901
R5, R6, R8: R10K; R_1206_3216Metric; MPN 1206W4F1002T5E; LCSC C17902
R12, R13: 5.1k; R_0603_1608Metric; MPN 0603WAF5101T5E; LCSC C23186
Serial1: HC-TYPE-C-16P-01A; USB_C_Receptacle_HCTL_HC-TYPE-C-16P-01A; MPN HC-TYPE-C-16P-01A; LCSC C2894897
TH1: 10k B3950; R_0805_2012Metric; MPN CMFB103J3950HANT; LCSC C338623
U1: ESP32-WROOM-32E-N4; ESP32-WROOM-32E; MPN ESP32-WROOM-32E-N4; LCSC C701341
U2: CH340C; SOIC-16_3.9x9.9mm_P1.27mm; MPN CH340C; LCSC C84681
U3: TLV1117LV33DCYR; SOT-223-3_TabPin2; MPN TLV1117LV33DCYR; LCSC C15578

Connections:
+3V3: C1.1, C5.1, C9.1, IN1.2, J1.1, J1.8, J2.1, R5.2, R6.2, R8.1, U1.2 (VDD), U2.4 (V3), U2.16 (VCC), U3.2 (VO)
+5V: C2.1, C3.1, C4.1, Serial1.A4 (VBUS), Serial1.A9 (VBUS), Serial1.B4 (VBUS), Serial1.B9 (VBUS), U3.3 (VI)
/ESP_BOOT: J2.6, R6.1, U1.25 (IO0)
/ESP_EN: C6.1, J2.5, R5.1, U1.3 (EN)
/RXD0_ESP: J2.4, U1.34 (RXD0/IO3)
/SPI_CS: J1.3, U1.23 (IO15)
/SPI_DC: J1.5, U1.14 (IO12)
/SPI_RESET: J1.4, U1.13 (IO14)
/SPI_SCK: J1.7, U1.30 (IO18)
/SPI_SDA: J1.6, U1.37 (IO23)
/TXD0_ESP: J2.3, U1.35 (TXD0/IO1)
/UART2_RX: U1.27 (IO16), U2.2 (TXD)
/UART2_TX: U1.28 (IO17), U2.3 (RXD)
/USB_DATA_DM: Serial1.A7 (D-), Serial1.B7 (D-), U2.6 (UD-)
/USB_DATA_DP: Serial1.A6 (D+), Serial1.B6 (D+), U2.5 (UD+)
GND: C1.2, C2.2, C3.2, C4.2, C5.2, C6.2, C9.2, D1.4 (GK), D1.5 (RK), D1.6 (BK), DA1.2 (B), J1.2, J2.2, R12.1, R13.1, Serial1.A1 (GND), Serial1.A12 (GND), Serial1.B1 (GND), Serial1.B12 (GND), Serial1.SH (SHIELD), TH1.1, U1.1 (GND), U1.15 (GND), U1.38 (GND), U1.39 (GND), U1.[1,15,38,39] (GND), U2.1 (GND), U2.15 (R232), U3.1 (GND)
unnamed: D1.1 (BA), R1.1
unnamed: D1.3 (GA), R3.1
unnamed: D1.2 (RA), R2.1
unnamed: DA1.1 (A), U1.8 (IO32)
unnamed: R13.2, Serial1.A5 (CC1)
unnamed: R12.2, Serial1.B5 (CC2)
unnamed: R1.2, U1.10 (IO25)
unnamed: R2.2, U1.11 (IO26)
unnamed: R3.2, U1.12 (IO27)
unnamed: IN1.1, U1.9 (IO33)
unnamed: R8.2, TH1.2, U1.6 (IO34)

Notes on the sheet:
Serial1 USB: application UART2 only. Programming uses external J2 UART0.
J2: 1=+3V3, 2=GND, 3=ESP TXD0, 4=ESP RXD0, 5=EN, 6=GPIO0. Programming: Serial1 USB disconnected; programmer powers J2 pin1 at regulated 3.3 V. Normal use: disconnect the programmer completely, then connect Serial1 USB. U3 OUT and J2 pin1 share +3V3 directly; no reverse-current isolation. Adapter TX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
EXTERNAL ESP32 UART0 PROGRAMMING / 3.3 V LOGIC ONLY
U3: TI TLV1117LV33DCYR (pin-compatible 1117 symbol). Keep this ceramic-stable regulator with MLCC output capacitor C5. C5: 22uF 25V X5R Basic; account for DC-bias derating.
Manual download via J2: connect pin6 (GPIO0) to pin2 (GND). Briefly connect pin5 (EN) to GND, then release EN with GPIO0 still low. Flash via UART0; release GPIO0 and pulse EN again for normal boot. R5/R6 pull-ups and C6 (1uF EN-to-GND) provide bias and reset timing. No on-board DTR/RTS auto-reset 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

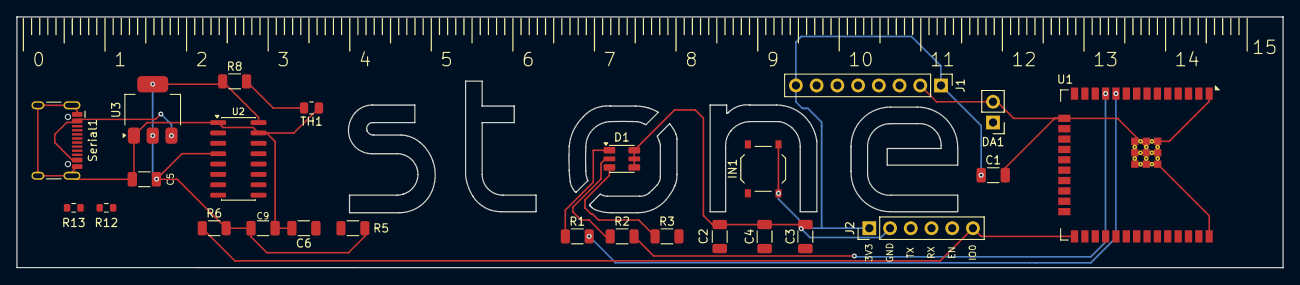
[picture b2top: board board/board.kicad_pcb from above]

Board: 2 copper layers, 155.2 x 30.7 mm, 25 parts (0 on the bottom side), 27 nets.
